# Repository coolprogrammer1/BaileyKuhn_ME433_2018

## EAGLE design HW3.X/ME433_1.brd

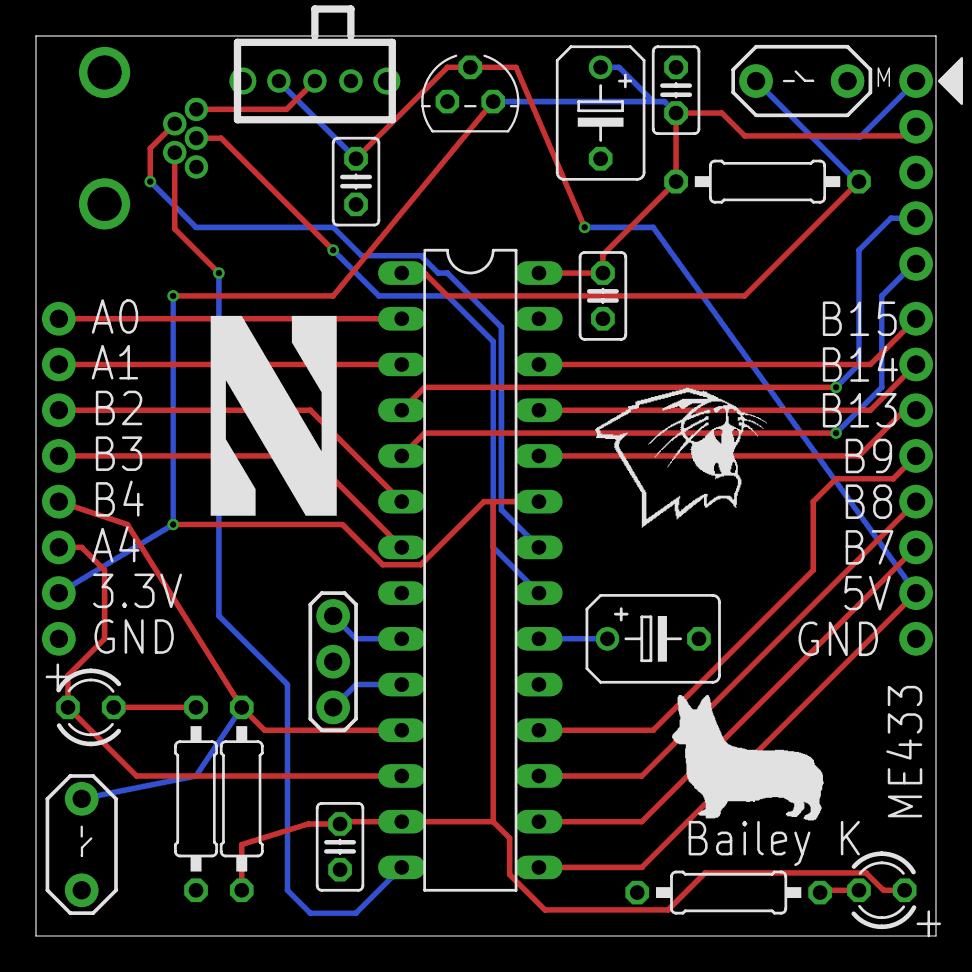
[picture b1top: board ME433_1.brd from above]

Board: 2 copper layers, 50.0 x 50.0 mm, 22 parts (0 on the bottom side), 27 nets.

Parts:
C1, C2, C3, C4: 0.1uF; C025-025X050
C5, C6: 10uF; B45181B
J1: USB-MB-H
J2, J3: 1X08
LED1: Red; LED3MM
LED2: Green; LED3MM
R1, R2: 330; 0207/10
R3, R4: 10k; 0207/10
U$1: PIC32MX250F128B; DIL28-3
U$2: SLIDE
U$3: MCP1702; TO92
U$4: RESET; PB
U$5: USER; PB
U$6: PICKIT3; 1X05
U$7: 8MHz; OSC

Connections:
+3V3: C1.1, C2.1, C4.1, C6.+, J3.2, LED1.A, R3.2, R4.2, U$1.13, U$1.23, U$1.28, U$3.3, U$6.2
+5V: C3.1, J2.2, U$1.15, U$2.1, U$3.2
A0: J3.8, U$1.2
A1: J3.7, U$1.3
A4/LED: J3.3, LED2.A, U$1.12
B2: J3.6, U$1.6
B3: J3.5, U$1.7
B4/USER: J3.4, R4.1, U$1.11, U$5.1
B7: J2.3, U$1.16
B8: J2.4, U$1.17
B9: J2.5, U$1.18
B13: J2.6, U$1.24
B14: J2.7, U$1.25
B15: J2.8, U$1.26
D+: J1.D+, U$1.21
D-: J1.D-, U$1.22
GND: C1.2, C2.2, C3.2, C4.2, C5.-, C6.-, J1.GND, J2.1, J3.1, R1.1, R2.1, U$1.8, U$1.19, U$1.27, U$3.1, U$4.2, U$5.2, U$6.3, U$7.2
MCLR: R3.1, U$1.1, U$4.1, U$6.1
unnamed: J1.VBUS, U$2.2
unnamed: LED1.K, R1.2
unnamed: LED2.K, R2.2
unnamed: U$1.9, U$7.1
unnamed: U$1.10, U$7.3
unnamed: C5.+, U$1.20
PGC: U$1.5, U$6.5
PGD: U$1.4, U$6.4
USBID: J1.ID, U$1.14

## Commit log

2018-04-06 working on HW1
2018-04-06 Added Photos for parts 1-6
2018-04-06 created main.c
2018-04-06 added #pragma values
2018-04-06 add TRIS and LAT commands to main
2018-04-07 added some core timer stuff
2018-04-07 added LED stuff
2018-04-07 adding button
2018-04-07 flipped button
2018-04-07 completed code
2018-04-11 Uploading Eagle files
    Couldn't save to GitHub directly so committing all at once
2018-04-14 Homework 3
    .brd and gerber files
2018-04-17 Homework 4 stuff and circuit schematic
2018-04-17 added some functions, initialization things
2018-04-17 altering previous code
2018-04-17 added SPI1_IO function
2018-04-17 setting up SDO pin
2018-04-17 trying to do some stuff with bits
2018-04-17 more bit stuff
2018-04-17 fixed some bit things
2018-04-18 debugging
2018-04-18 CS stuff
2018-04-18 trying to figure out what voltage means
2018-04-18 bit shifting
2018-04-18 sine wave
2018-04-19 triangle wave
2018-04-19 more triangle
2018-04-19 figuring out frequency stuff
2018-04-19 got sine freq. now triangle
2018-04-19 got triangle working on sine
2018-04-19 final code!
2018-04-19 new folder and circuit schematic
2018-04-19 creating code
2018-04-19 change to i2c2
2018-04-19 altering main.c while loop
2018-04-19 write functions
2018-04-19 light blinking but i2c not working
2018-04-20 testing write function
2018-04-20 writing works
2018-04-25 new folder
2018-04-25 drawChar
2018-04-25 drawString
2018-04-25 circuit diagram
2018-04-25 start to get code running
2018-04-25 drawPixel works!
2018-04-25 drawChar works!
2018-04-25 drawString debugging
2018-04-26 trying to update at 10Hz
2018-04-26 debugging counter
2018-04-26 just needed to add spaces!
2018-04-26 working on progress bar
2018-04-26 still progress bar
2018-04-26 progress bar works!
2018-04-26 new HW and writing readMultiple
2018-04-26 initializing registers
2018-04-26 trying to read who am i
2018-04-26 debug flashing screen
2018-04-26 fixed sprintf
2018-04-29 trying multiple read
2018-04-29 all values are updating
2018-04-29 testing bar in x
2018-04-29 timing weird
2018-05-01 debugging progress bars
2018-05-01 x bar is working!
2018-05-01 trying the y
2018-05-01 it works!
2018-05-01 created folder and project and adding #pragma values
2018-05-01 initialize and add blinking code
2018-05-01 blinking and pushbutton works!
2018-05-01 HW7 works!
2018-05-03 done
2018-05-03 made project + pragma
2018-05-03 setting up USB stuff
2018-05-03 replacing code with given code
2018-05-03 replace2
2018-05-03 adding some initialization stuff to app.c
2018-05-03 added some initialization code
2018-05-03 reading from IMU
2018-05-03 making a write loop
2018-05-03 not sure how to loop
2018-05-03 changing timing
2018-05-03 try code later
2018-05-05 Checking if I can read numbers
2018-05-05 looping but not stopping after 100, when I put set=0 nothing shows
2018-05-06 changing the loops
2018-05-06 loop works
2018-05-08 making HW 10
2018-05-09 editing
2018-05-09 refining loops
2018-05-09 trying to print things
2018-05-09 all data outputting!
2018-05-09 code works
2018-05-10 create project
2018-05-10 add given files
2018-05-10 initializing
2018-05-10 given code works
2018-05-10 IMU data not translating
2018-05-10 code works!
2018-05-15 starter code works!
2018-05-15 added code
2018-05-17 original code works. Added seekbar
2018-05-17 added for loop and 5 rows
2018-05-17 working
2018-05-22 made new project
2018-05-22 inserted code into cdc code
2018-05-22 creating android code
2018-05-22 adding USB
2018-05-23 added button
2018-05-24 CAD Photos
2018-05-29 laser cut box
2018-05-29 wheel
2018-06-05 HW17
2018-06-05 video
2018-06-05 HW18 USB code
2018-06-07 adding PWM code
2018-06-07 motor control initialization code
2018-06-12 added photos
2018-06-12 photos
